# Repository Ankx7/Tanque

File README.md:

# Tanque
Tanque controlado con Jetson y Nano Arduino

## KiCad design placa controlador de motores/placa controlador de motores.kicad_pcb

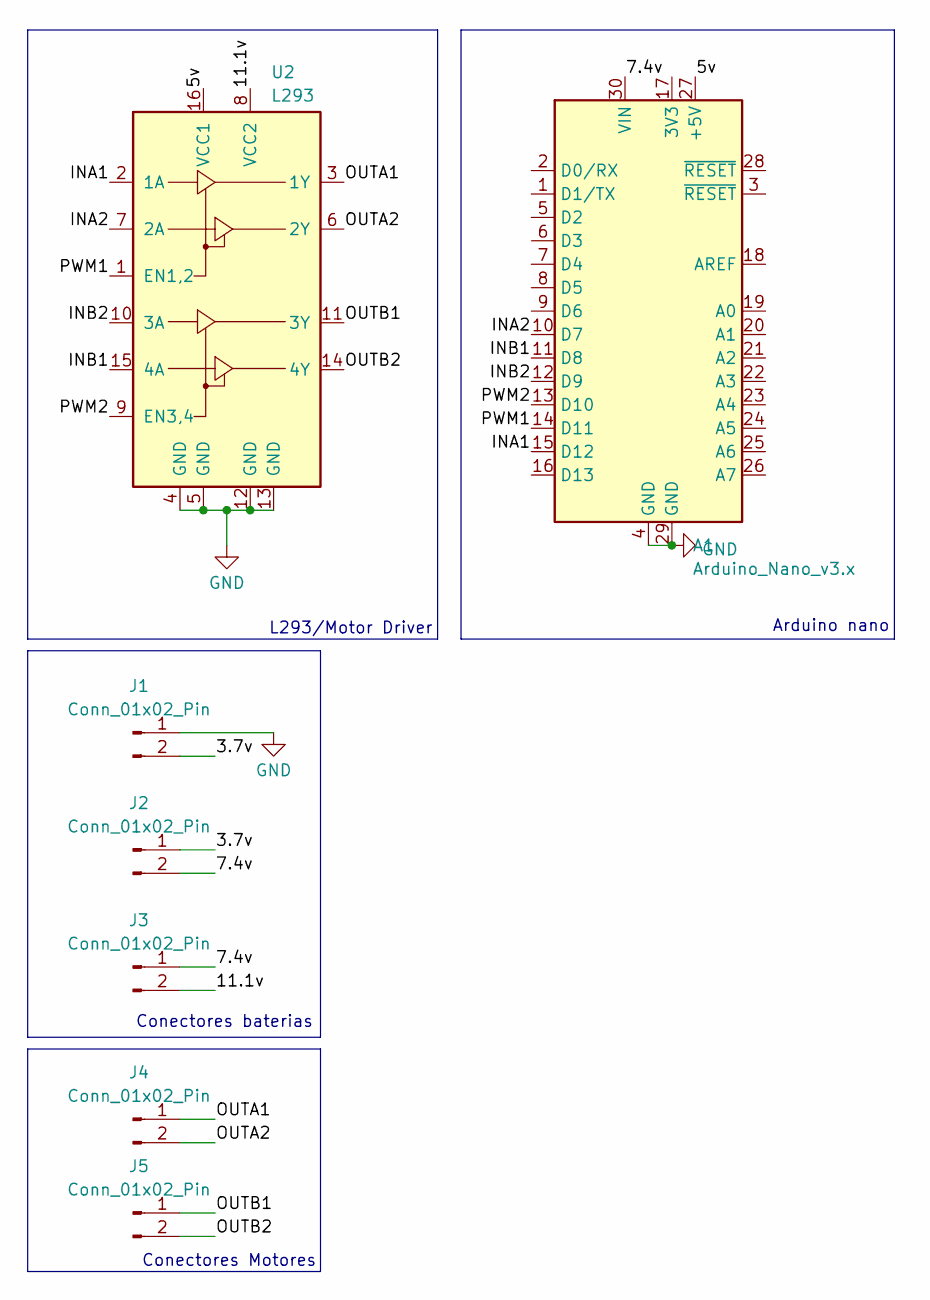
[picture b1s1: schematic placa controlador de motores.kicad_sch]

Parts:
A1: Arduino_Nano_v3.x; Arduino_Nano
J1, J2, J3, J4, J5: Conn_01x02_Pin; PinSocket_1x02_P2.54mm_Vertical
U2: L293; DIP-16_W7.62mm

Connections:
/3.7v: J1.2, J2.1
/5v: A1.27 (+5V), U2.16 (VCC1)
/7.4v: A1.30 (VIN), J2.2, J3.1
/11.1v: J3.2, U2.8 (VCC2)
/INA1: A1.15 (D12), U2.2 (1A)
/INA2: A1.10 (D7), U2.7 (2A)
/INB1: A1.11 (D8), U2.15 (4A)
/INB2: A1.12 (D9), U2.10 (3A)
/OUTA1: J4.1, U2.3 (1Y)
/OUTA2: J4.2, U2.6 (2Y)
/OUTB1: J5.1, U2.11 (3Y)
/OUTB2: J5.2, U2.14 (4Y)
/PWM1: A1.14 (D11), U2.1 (EN1,2)
/PWM2: A1.13 (D10), U2.9 (EN3,4)
GND: A1.4 (GND), A1.29 (GND), J1.1, U2.4 (GND), U2.5 (GND), U2.12 (GND), U2.13 (GND)

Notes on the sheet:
Conectores baterias
Arduino nano
Conectores Motores
L293/Motor Driver

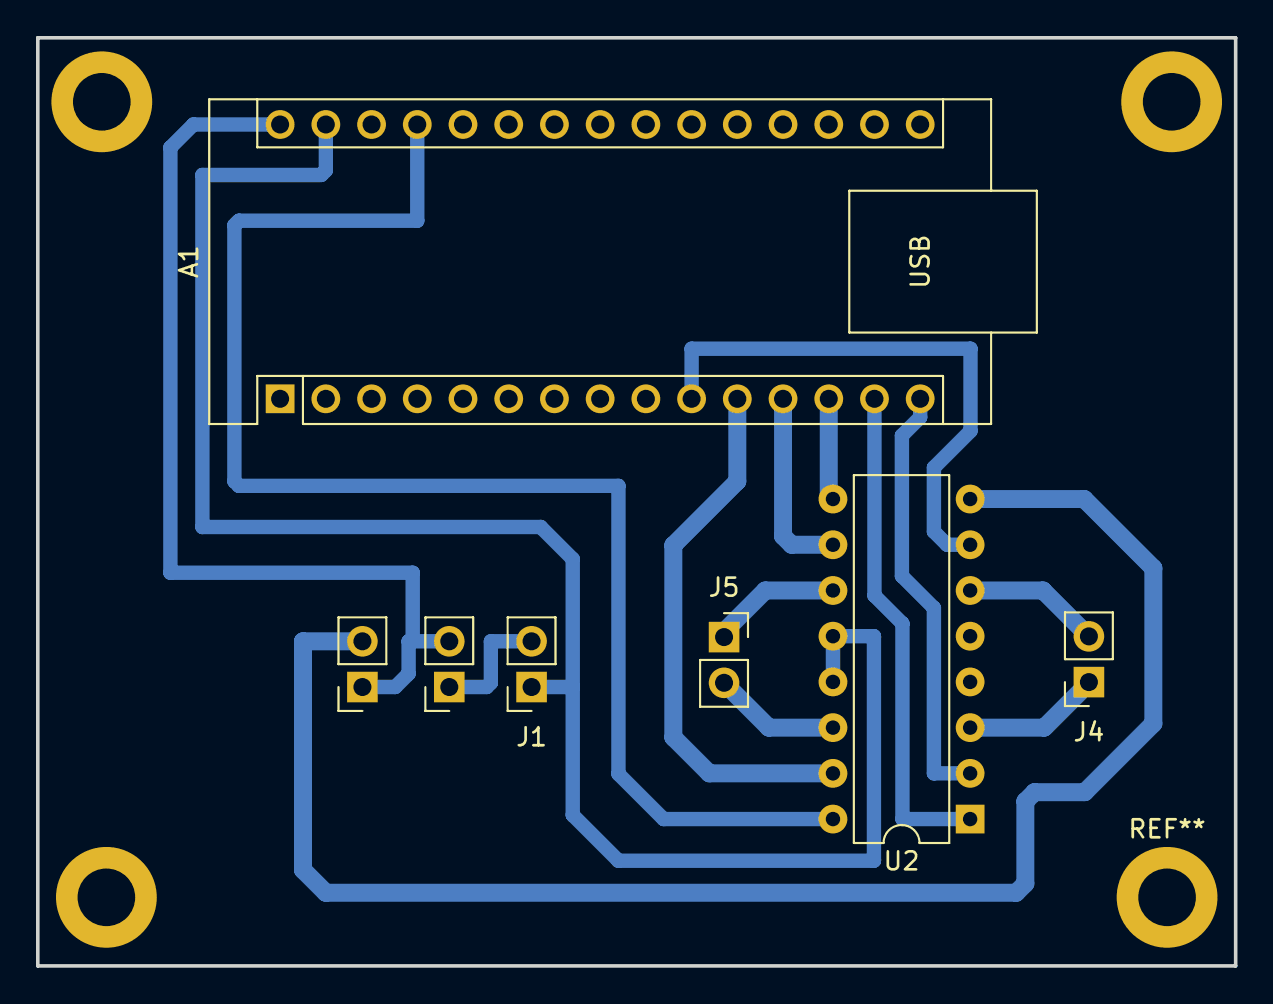
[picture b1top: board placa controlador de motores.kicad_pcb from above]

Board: 2 copper layers, 66.5 x 51.6 mm, 7 parts (0 on the bottom side), 15 nets.

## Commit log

2024-06-10 Update and rename README.md to Conexión
2024-06-10 Create Links
2024-06-10 Create Prueba motores
2024-06-10 Update Links
2024-07-14 falta ver motor derecho raro
